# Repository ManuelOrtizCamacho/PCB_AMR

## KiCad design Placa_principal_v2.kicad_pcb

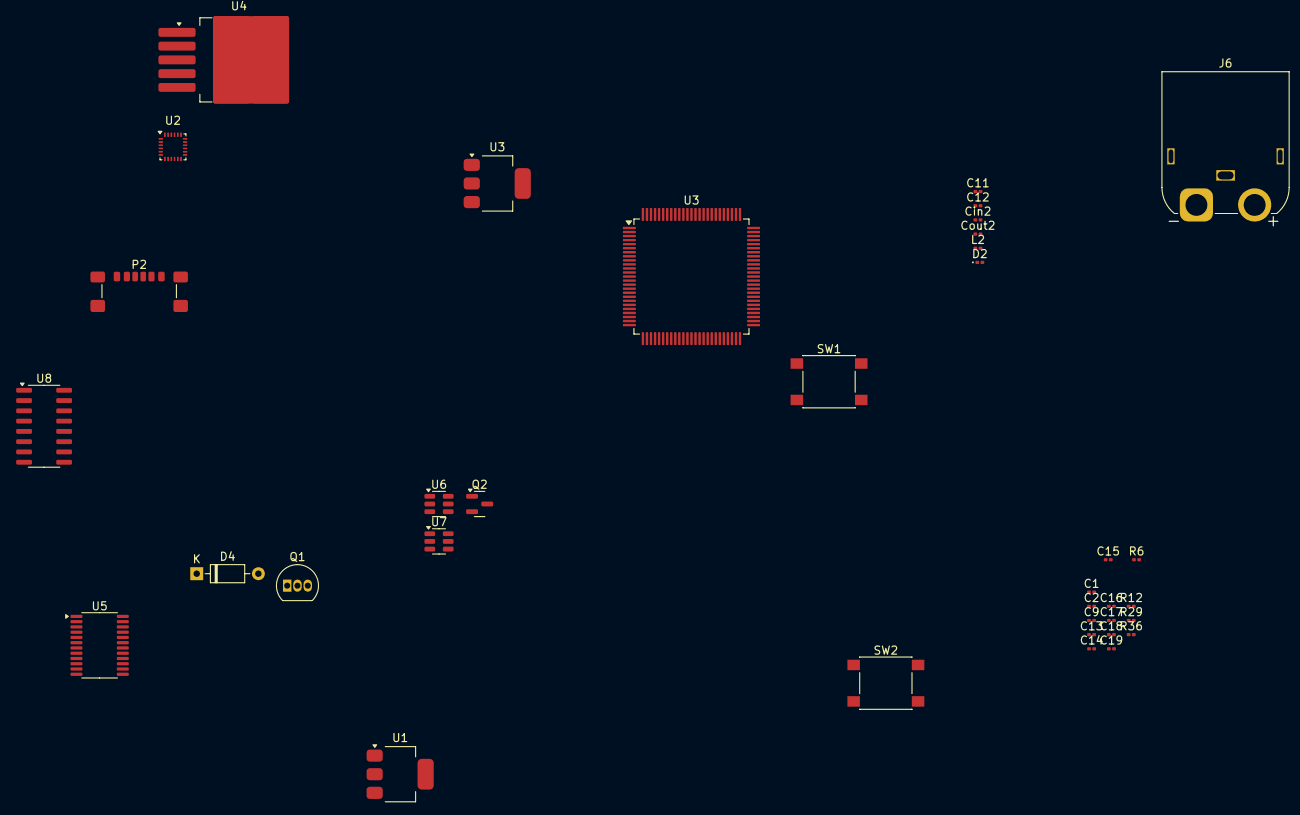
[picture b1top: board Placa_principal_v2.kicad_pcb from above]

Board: 2 copper layers, 36 parts (0 on the bottom side), 18 nets, no tracks yet.

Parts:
C1, C2, C9, C13, C14, C15, C16, C18, C19: 100nF; C_0201_0603Metric
C11, C12: 10uF; C_0201_0603Metric
C17: 1uF; C_0201_0603Metric
Cin2: 220uF; C_0201_0603Metric
Cout2: 220uF; C_0201_0603Metric
D2: 1N5822; D_0201_0603Metric
D4: 1N4148; D_DO-35_SOD27_P7.62mm_Horizontal
J6: Input 12V-24V connector; AMASS_XT60IPW-M_1x03_P7.20mm_Horizontal
L2: 33uH; L_0201_0603Metric
P2: USB_C_Plug_USB2.0; USB_C_Receptacle_GCT_USB4135-GF-A_6P_TopMnt_Horizontal
Q1: S8050; TO-92_Inline
Q2: IRLML6402; SOT-23
R6, R12, R36: 10k; R_0201_0603Metric
R29: 1k; R_0201_0603Metric
SW1, SW2: SW_Push; SW_SPST_PTS645
U1, U3#2: LM1117MP-3.3; SOT-223-3_TabPin2
U2: ICM-20948; InvenSense_QFN-24_3x3mm_P0.4mm
U3: STM32F407VGTx; LQFP-100_14x14mm_P0.5mm
U4: LM2596S-5; TO-263-5_TabPin3
U5: TCA9548APWR; TSSOP-24_4.4x7.8mm_P0.65mm
U6, U7: USBLC6-2SC6; SOT-23-6
U8: CH340G; SOIC-16_3.9x9.9mm_P1.27mm

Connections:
3.3V: C1.2, C2.2, C12.1, C13.2, C14.2, C15.2, C18.2, C19.2, Q2.2 (S), Q2.3 (D), R6.1, SW2.2, U1.2 (VO), U2.8 (VDDIO), U2.13 (VDD), U2.22 (~CS), U3.6 (VBAT), U3.11 (VDD), U3.19 (VDD), U3.28 (VDD), U3.50 (VDD), U3.75 (VDD), U3.100 (VDD), U3#2.2 (VO), U5.24 (VCC), U8.4 (V3), U8.16 (VCC)
5V: C11.1, Cout2.1, D4.1 (K), L2.2, U1.3 (VI), U3#2.3 (VI)
GND: C1.1, C2.1, C9.1, C11.2, C12.2, C13.1, C14.1, C15.1, C16.1, C17.1, C18.1, C19.1, Cin2.2, Cout2.2, D2.2 (A), J6.1, P2.A12 (GND), P2.B12 (GND), P2.S1 (SHIELD), Q1.1 (E), R12.1, R36.2, SW1.1, SW2.1, U1.1 (GND), U2.9 (SDO/AD0), U2.18 (GND), U2.20 (GND), U3.10 (VSS), U3.20 (VSSA), U3.27 (VSS), U3.74 (VSS), U3.99 (VSS), U3#2.1 (GND), U4.3 (GND), U4.5 (~ON/OFF), U5.1 (A0), U5.2 (A1), U5.12 (GND), U5.21 (A2), U6.2 (GND), U7.2 (GND), U8.1 (GND)
NRST: C9.2, R6.2, SW1.2, U3.14 (NRST)
unnamed: D4.2 (A), Q1.3 (C)
unnamed: P2.A9 (VBUS), P2.B9 (VBUS), U7.1 (I/O1), U7.5 (VBUS), U8.5 (UD+)
unnamed: D2.1 (K), L2.1, U4.2 (OUT)
unnamed: Cin2.1, J6.2, U4.1 (VIN)
unnamed: Q1.2 (B), R29.2
unnamed: R12.2, U3.94 (BOOT0)
unnamed: R36.1, U3.37 (PB2)
unnamed: C16.2, C17.2, U3.22 (VDDA)
unnamed: U7.3 (I/O2), U8.6 (UD-)
PA6: R29.1, U3.31 (PA6)
PB6: U3.92 (PB6), U5.22 (SCL)
PB7: U3.93 (PB7), U5.23 (SDA)
PB10: U2.23 (SCL/SCLK), U3.47 (PB10), U8.2 (TXD)
PB11: U2.24 (SDA/SDI), U3.48 (PB11), U8.3 (RXD)

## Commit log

2025-05-27 buenas
2025-05-27 .gitignore setup
2025-05-27 git plugin test
2025-06-12 Revision 110625
